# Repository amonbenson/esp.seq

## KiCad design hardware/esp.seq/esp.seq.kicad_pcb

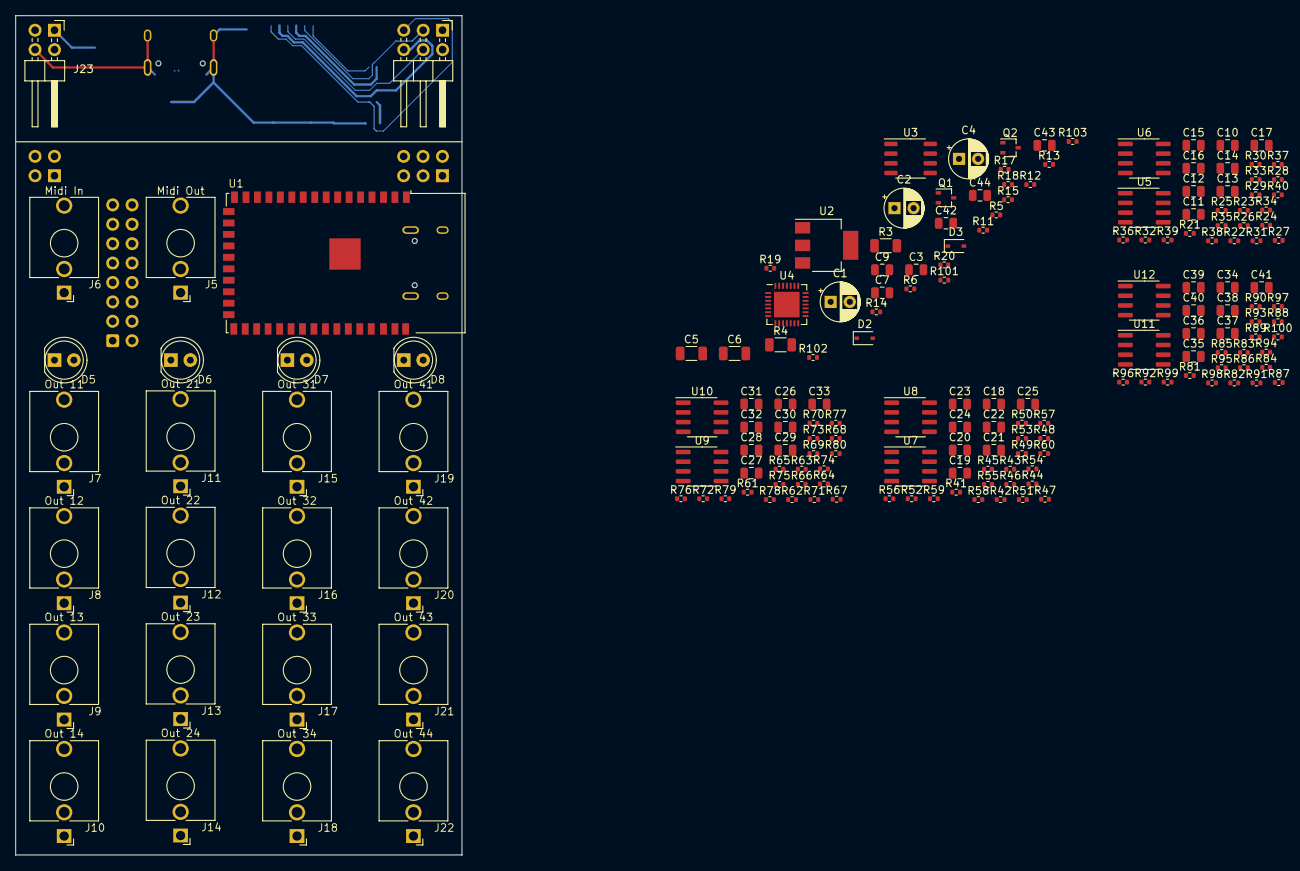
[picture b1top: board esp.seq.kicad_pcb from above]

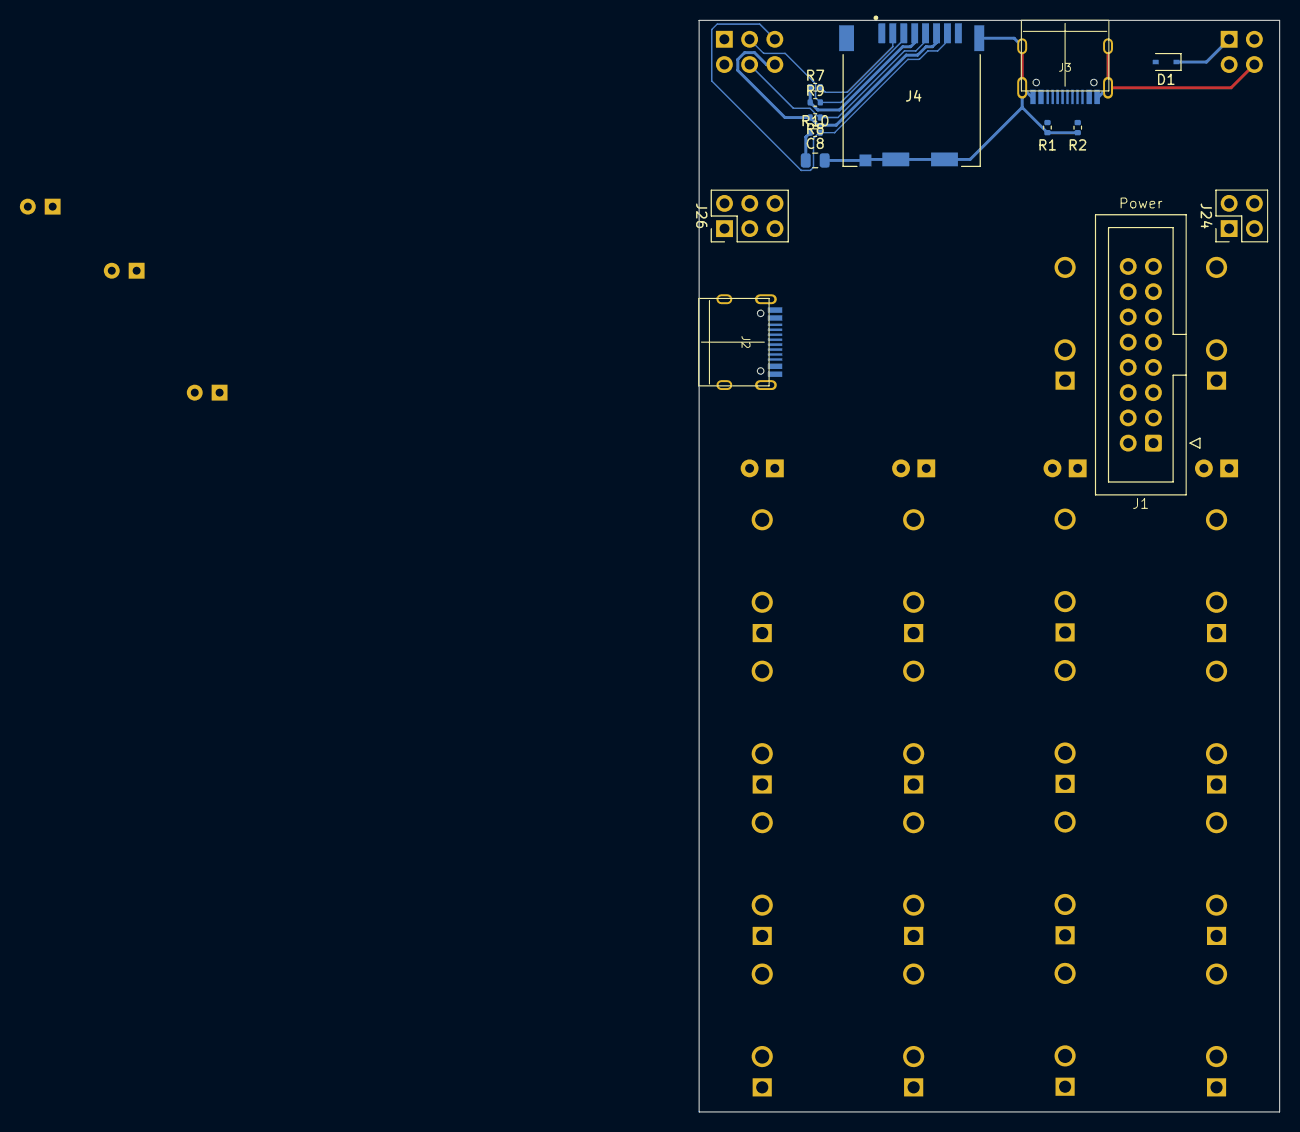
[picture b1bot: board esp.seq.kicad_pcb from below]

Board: 2 copper layers, 58.4 x 109.9 mm, 193 parts (14 on the bottom side), 149 nets.

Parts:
C1, C2, C4: 10u; CP_Radial_D5.0mm_P2.50mm
C3, C7, C8, C44: 100n; C_0805_2012Metric
C5, C6: 22u; C_1206_3216Metric
C9, C42: 1u; C_0805_2012Metric
C10, C12, C14, C16, C18, C20, C22, C24, C26, C28, C30, C32, C34, C36, C38, C40: 470n; C_0805_2012Metric
C11, C13, C15, C17, C19, C21, C23, C25, C27, C29, C31, C33, C35, C37, C39, C41: 220n; C_0805_2012Metric
C43: 10u; C_0805_2012Metric
D1, D3: 1N5819WS; D_SOD-323
D2: 1N4148WS; D_SOD-323
D5, D6, D7, D8: LED_Red; LED_D5.0mm
J1: Conn_02x08; IDC-Header_2x08_P2.54mm_Vertical
J2, J3: USB-C; TYPE-C-31-M-12
J4: Micro_SD_Card; HRS_DM3CS-SF
J5, J6: PJ-301M-3
J7, J8, J9, J10, J11, J12, J13, J14, J15, J16, J17, J18, J19, J20, J21, J22: PJ-301M-2
J23: Conn_01x04_Male; PinHeader_2x02_P2.54mm_Horizontal
J24: Conn_01x04_Male; PinHeader_2x02_P2.54mm_Vertical
J25: Conn_01x06_Male; PinHeader_2x03_P2.54mm_Horizontal
J26: Conn_01x06_Male; PinHeader_2x03_P2.54mm_Vertical
Q1, Q2: SS8050; SOT-323_SC-70
R1, R2, R11, R12: 5.1k; R_0402_1005Metric
R3, R4: 47; R_1206_3216Metric
R5, R17, R18, R19, R20: 220; R_0402_1005Metric
R6: 470; R_0402_1005Metric
R7, R8, R9, R10, R14: 47k; R_0402_1005Metric
R13: 22k; R_0402_1005Metric
R15, R25, R30, R35, R40, R45, R50, R55, R60, R65, R70, R75, R80, R85, R90, R95, R100: 1k; R_0402_1005Metric
R21, R22, R26, R27, R31, R32, R36, R37, R41, R42, R46, R47, R51, R52, R56, R57, R61, R62, R66, R67, R71, R72, R76, R77, R81, R82, R86, R87, R91, R92, R96, R97, R101, R102, R103: 10k; R_0402_1005Metric
R23, R28, R33, R38, R43, R48, R53, R58, R63, R68, R73, R78, R83, R88, R93, R98: 220k; R_0402_1005Metric
R24, R34, R44, R54, R64, R74, R84, R94: 330k; R_0402_1005Metric
R29, R39, R49, R59, R69, R79, R89, R99: 100k; R_0402_1005Metric
U1: ESP32-S2-WROVER
U2: AMS1117-3.3; SOT-223-3_TabPin2
U3: 6N137; SO-8_3.9x4.9mm_P1.27mm
U4: CP2102; QFN-28-1EP_5x5mm_P0.5mm_EP3.35x3.35mm
U5, U6, U7, U8, U9, U10, U11, U12: TL072; SOIC-8_3.9x4.9mm_P1.27mm

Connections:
+3.3V: C6.1, C43.2, C44.2, J26.1, R3.2, R6.1, R15.1, R103.2, U1.2 (3V3), U2.2 (VO), U4.6 (VDD), U4.7 (VREGIN)
+5V: C4.1, C5.1, C7.1, D3.1 (K), J1.11, J1.12, J24.1, U2.3 (VI), U3.8 (VCC)
+12V: C1.1, C3.2, J1.9, J1.10, U5.8 (V+), U6.8 (V+), U7.8 (V+), U8.8 (V+), U9.8 (V+), U10.8 (V+), U11.8 (V+), U12.8 (V+)
-12V: C2.2, C3.1, J1.1, J1.2, U5.4 (V-), U6.4 (V-), U7.4 (V-), U8.4 (V-), U9.4 (V-), U10.4 (V-), U11.4 (V-), U12.4 (V-)
/CON_+3.3V: C8.1, J4.4 (VDD), J25.1, R7.1, R9.1, R10.1
/CON_+5V: D1.1 (K), J23.1
/CON_FSPI_CLK: J4.5 (CLK), J25.4, R8.1
/CON_FSPI_CS: J4.2 (DAT3/CD), J25.2, R7.2
/CON_FSPI_MISO: J4.7 (DAT0), J25.5, R10.2
/CON_FSPI_MOSI: J4.3 (CMD), J25.3, R9.2
/CON_USB_D+: J3.A6 (D+), J3.B6 (D+), J23.3
/CON_USB_D-: J3.A7 (D-), J3.B7 (D-), J23.2
/CON_VBUS: D1.2 (A), J3.A4 (VBUS), J3.A9 (VBUS), J3.B4 (VBUS), J3.B9 (VBUS)
DTR: Q2.2 (E), R101.1, U4.28 (~DTR)
EN: C42.1, Q1.3 (C), R103.1, U1.41 (EN)
FSPI_CLK: J26.4, U1.30 (IO36)
FSPI_CS: J26.2, U1.28 (IO34)
FSPI_MISO: J26.5, U1.31 (IO37)
FSPI_MOSI: J26.3, U1.29 (IO35)
GND: C1.2, C2.1, C4.2, C5.2, C6.2, C7.2, C9.2, C11.2, C13.2, C15.2, C17.2, C19.2, C21.2, C23.2, C25.2, C27.2, C29.2, C31.2, C33.2, C35.2, C37.2, C39.2, C41.2, C42.2, C43.1, C44.1, D5.1 (K), D6.1 (K), D7.1 (K), D8.1 (K), J1.3, J1.4, J1.5, J1.6, J1.7, J1.8, J2.A1 (GND), J2.A12 (GND), J2.B1 (GND), J2.B12 (GND), J2.S1 (SHIELD), J5.S, J7.S, J8.S, J9.S, J10.S, J11.S, J12.S, J13.S, J14.S, J15.S, J16.S, J17.S, J18.S, J19.S, J20.S, J21.S, J22.S, J24.4, J26.6, R11.2, R12.2, R14.1, R24.2, R29.2, R34.2, R39.2, R44.2, R49.2, R54.2, R59.2, R64.2, R69.2, R74.2, R79.2, R84.2, R89.2, R94.2, R99.2, U1.1 (GND), U1.26 (GND), U1.42 (GND), U1.43 (GND), U2.1 (GND), U3.5 (GND), U4.3 (GND), U4.29 (GND)
GND1: C8.2, J3.A1 (GND), J3.A12 (GND), J3.B1 (GND), J3.B12 (GND), J3.S1 (SHIELD), J4.6 (VSS), J4.9 (SHIELD), J23.4, J25.6, R1.2, R2.2, R8.2
IO0: Q2.3 (C), U1.3 (IO00)
IO1: R21.1, U1.4 (IO01)
IO2: R26.1, U1.5 (IO02)
IO3: R31.1, U1.6 (IO03)
IO4: R36.1, U1.7 (IO04)
IO5: R41.1, U1.8 (IO05)
IO6: R46.1, U1.9 (IO06)
IO7: R51.1, U1.10 (IO07)
IO8: R56.1, U1.11 (IO08)
IO9: R61.1, U1.12 (IO09)
IO10: R66.1, U1.13 (IO10)
IO11: R71.1, U1.14 (IO11)
IO12: R76.1, U1.15 (IO12)
IO13: R81.1, U1.16 (IO13)
IO14: R86.1, U1.17 (IO14)
IO15: R91.1, U1.18 (IO15)
IO16: R96.1, U1.19 (IO16)
IO39: R17.1, U1.33 (IO39)
IO40: R18.1, U1.34 (IO40)
IO41: R19.1, U1.35 (IO41)
IO42: R20.1, U1.36 (IO42)
unnamed: C9.1, R13.1, R14.2, U4.8 (VBUS)
unnamed: C10.1, R23.1, R25.1, U5.1
unnamed: C10.2, R21.2, R22.1
unnamed: C11.1, R22.2, U5.3 (+)
unnamed: C12.1, R28.1, R30.1, U5.7
unnamed: C12.2, R26.2, R27.1
unnamed: C13.1, R27.2, U5.5 (+)
unnamed: C14.1, R33.1, R35.1, U6.1
unnamed: C14.2, R31.2, R32.1
unnamed: C15.1, R32.2, U6.3 (+)
unnamed: C16.1, R38.1, R40.1, U6.7
unnamed: C16.2, R36.2, R37.1
unnamed: C17.1, R37.2, U6.5 (+)
unnamed: C18.1, R43.1, R45.1, U7.1
unnamed: C18.2, R41.2, R42.1
unnamed: C19.1, R42.2, U7.3 (+)
unnamed: C20.1, R48.1, R50.1, U7.7
unnamed: C20.2, R46.2, R47.1
unnamed: C21.1, R47.2, U7.5 (+)
unnamed: C22.1, R53.1, R55.1, U8.1
unnamed: C22.2, R51.2, R52.1
unnamed: C23.1, R52.2, U8.3 (+)
unnamed: C24.1, R58.1, R60.1, U8.7
unnamed: C24.2, R56.2, R57.1
unnamed: C25.1, R57.2, U8.5 (+)
unnamed: C26.1, R63.1, R65.1, U9.1
unnamed: C26.2, R61.2, R62.1
unnamed: C27.1, R62.2, U9.3 (+)
unnamed: C28.1, R68.1, R70.1, U9.7
unnamed: C28.2, R66.2, R67.1
unnamed: C29.1, R67.2, U9.5 (+)
unnamed: C30.1, R73.1, R75.1, U10.1
unnamed: C30.2, R71.2, R72.1
unnamed: C31.1, R72.2, U10.3 (+)
unnamed: C32.1, R78.1, R80.1, U10.7
unnamed: C32.2, R76.2, R77.1
unnamed: C33.1, R77.2, U10.5 (+)
unnamed: C34.1, R83.1, R85.1, U11.1
unnamed: C34.2, R81.2, R82.1
unnamed: C35.1, R82.2, U11.3 (+)
unnamed: C36.1, R88.1, R90.1, U11.7
unnamed: C36.2, R86.2, R87.1
unnamed: C37.1, R87.2, U11.5 (+)
unnamed: C38.1, R93.1, R95.1, U12.1
unnamed: C38.2, R91.2, R92.1
unnamed: C39.1, R92.2, U12.3 (+)
unnamed: C40.1, R98.1, R100.1, U12.7
unnamed: C40.2, R96.2, R97.1
unnamed: C41.1, R97.2, U12.5 (+)
unnamed: D2.1 (K), R5.2, U3.2 (A)
unnamed: D2.2 (A), J5.T, U3.3 (C)
unnamed: D5.2 (A), R17.2
unnamed: D6.2 (A), R18.2
unnamed: D7.2 (A), R19.2
unnamed: D8.2 (A), R20.2
unnamed: J2.A5 (CC1), R12.1
unnamed: J2.B5 (CC2), R11.1
unnamed: J3.A5 (CC1), R2.1
unnamed: J3.B5 (CC2), R1.1
unnamed: J5.R, R5.1
unnamed: J6.R, R3.1
unnamed: J6.T, R4.1
unnamed: Q1.1 (B), R101.2
unnamed: Q2.1 (B), R102.2
unnamed: R15.2, U4.9 (~RST)
unnamed: R23.2, R24.1, U5.2 (-)
unnamed: R28.2, R29.1, U5.6 (-)
unnamed: R33.2, R34.1, U6.2 (-)
unnamed: R38.2, R39.1, U6.6 (-)
unnamed: R43.2, R44.1, U7.2 (-)
unnamed: R48.2, R49.1, U7.6 (-)
unnamed: R53.2, R54.1, U8.2 (-)
unnamed: R58.2, R59.1, U8.6 (-)
unnamed: R63.2, R64.1, U9.2 (-)
unnamed: R68.2, R69.1, U9.6 (-)
unnamed: R73.2, R74.1, U10.2 (-)
unnamed: R78.2, R79.1, U10.6 (-)
unnamed: R83.2, R84.1, U11.2 (-)
unnamed: R88.2, R89.1, U11.6 (-)
unnamed: R93.2, R94.1, U12.2 (-)
unnamed: R98.2, R99.1, U12.6 (-)
OUT11: J7.T, R25.2
OUT12: J8.T, R30.2
OUT13: J9.T, R35.2
OUT14: J10.T, R40.2
OUT21: J11.T, R45.2
OUT22: J12.T, R50.2
OUT23: J13.T, R55.2
OUT24: J14.T, R60.2
OUT31: J15.T, R65.2
OUT32: J16.T, R70.2
OUT33: J17.T, R75.2
OUT34: J18.T, R80.2
OUT41: J19.T, R85.2
OUT42: J20.T, R90.2
OUT43: J21.T, R95.2
OUT44: J22.T, R100.2
RTS: Q1.2 (E), R102.1, U4.24 (~RTS)
U0RXD: U1.38 (RXD0), U4.26 (TXD)
U0TXD: U1.37 (TXD0), U4.25 (RXD)
U1RXD: R6.2, U1.21 (IO18), U3.6 (VO)
U1TXD: R4.2, U1.20 (IO17)
UART_D+: J2.A6 (D+), J2.B6 (D+)
UART_D-: J2.A7 (D-), J2.B7 (D-), U4.4 (D+), U4.5 (D-)
USB_D+: J24.3, U1.23 (USB_D+)
USB_D-: J24.2, U1.22 (USB_D-)
VBUS: D3.2 (A), J2.A4 (VBUS), J2.A9 (VBUS), J2.B4 (VBUS), J2.B9 (VBUS), R13.2

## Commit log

2022-04-28 output channels now working
2022-05-01 interpolation working
2022-05-01 dacs now working on all channels
2022-05-02 flashing via uart1 finally working
2022-05-02 added usb basic config, removed debug info from channel
2022-05-02 usb device open close cycle working
2022-05-02 using queues now
2022-05-02 added usb descriptor parsing
2022-05-02 cleared readme
2022-05-02 interface claiming working
2022-05-02 usb midi in working
2022-05-03 project restructuring
2022-05-03 restructure of midi driver
2022-05-03 added connected/disconnected callbacks
2022-05-03 added additional callbacks
2022-05-03 more renames
2022-05-03 added support for sysex messages
2022-05-03 sysex receiving now working
2022-05-03 addded basic note on/off out commands
2022-05-05 large refactoring of the midi engine
2022-05-05 added tasks, some bugfixes
2022-05-06 implementing usb midi queues
2022-05-08 implemented basic output queue for testing
2022-05-09 tmp queues get parsed, not quite working yet
2022-05-09 changed semaphore handling in out packet loop
2022-05-09 output queue now fully working
2022-05-09 sysex working
2022-05-09 finished usb midi system
2022-05-10 usb midi bugfixes
2022-05-10 added simple monophonic midi to cv on channel 0
2022-05-10 first live tests
2022-05-28 reworked dac communication
2022-05-30 basic test sequencer working
2022-05-31 added basic event system to sequencer
2022-05-31 added track events
2022-10-09 preparing pwm version
2022-10-20 new output components, untested
2022-10-22 included previous sequencer
2022-10-22 sequencer working, seems to panic after some time
2022-10-23 added gate and probability settings to steps, bugfixes
2022-10-23 updated eventing pipeline
2022-10-28 first working tests
2022-10-29 reworked output module to be more generic
2022-10-29 reworked pin layout
2022-10-29 fixes, more notes
2022-11-01 added kicad files
2022-11-01 progress
2022-11-02 footprint and layout updates
2022-11-18 added usb midi and controller support
2022-11-18 added pwm control
2022-11-18 reworked sequencer event routing
2022-11-19 added launchpad controller
2022-11-21 switched to new callback system
2022-11-27 added sysex messages to clear launchpad on connection
2022-12-19 improved launchpad controller
2022-12-19 refectored launchpad ui
2022-12-19 added support for different tracks in pattern editor
2022-12-20 added separate lpui component
2022-12-20 updated render pipeline using callbacks
2022-12-20 updates to sysex functions
2022-12-20 added separate class for ui components
2022-12-20 pattern editor component now working
2022-12-20 added more efficient step drawing function, bugfixes
2022-12-20 outsourced piano editor to separate class
2022-12-20 added basic toggle functionality
2022-12-21 updated pattern editor redraw method
2022-12-21 added play button
2022-12-21 improved sequencer seeking and step selection
2022-12-22 added kconfig default file
2022-12-22 added custom Kconfig file
2022-12-22 moved kconfig file
2022-12-23 Added kconfig
2024-04-14 added gitpod files
2024-04-14 updated cpp props
